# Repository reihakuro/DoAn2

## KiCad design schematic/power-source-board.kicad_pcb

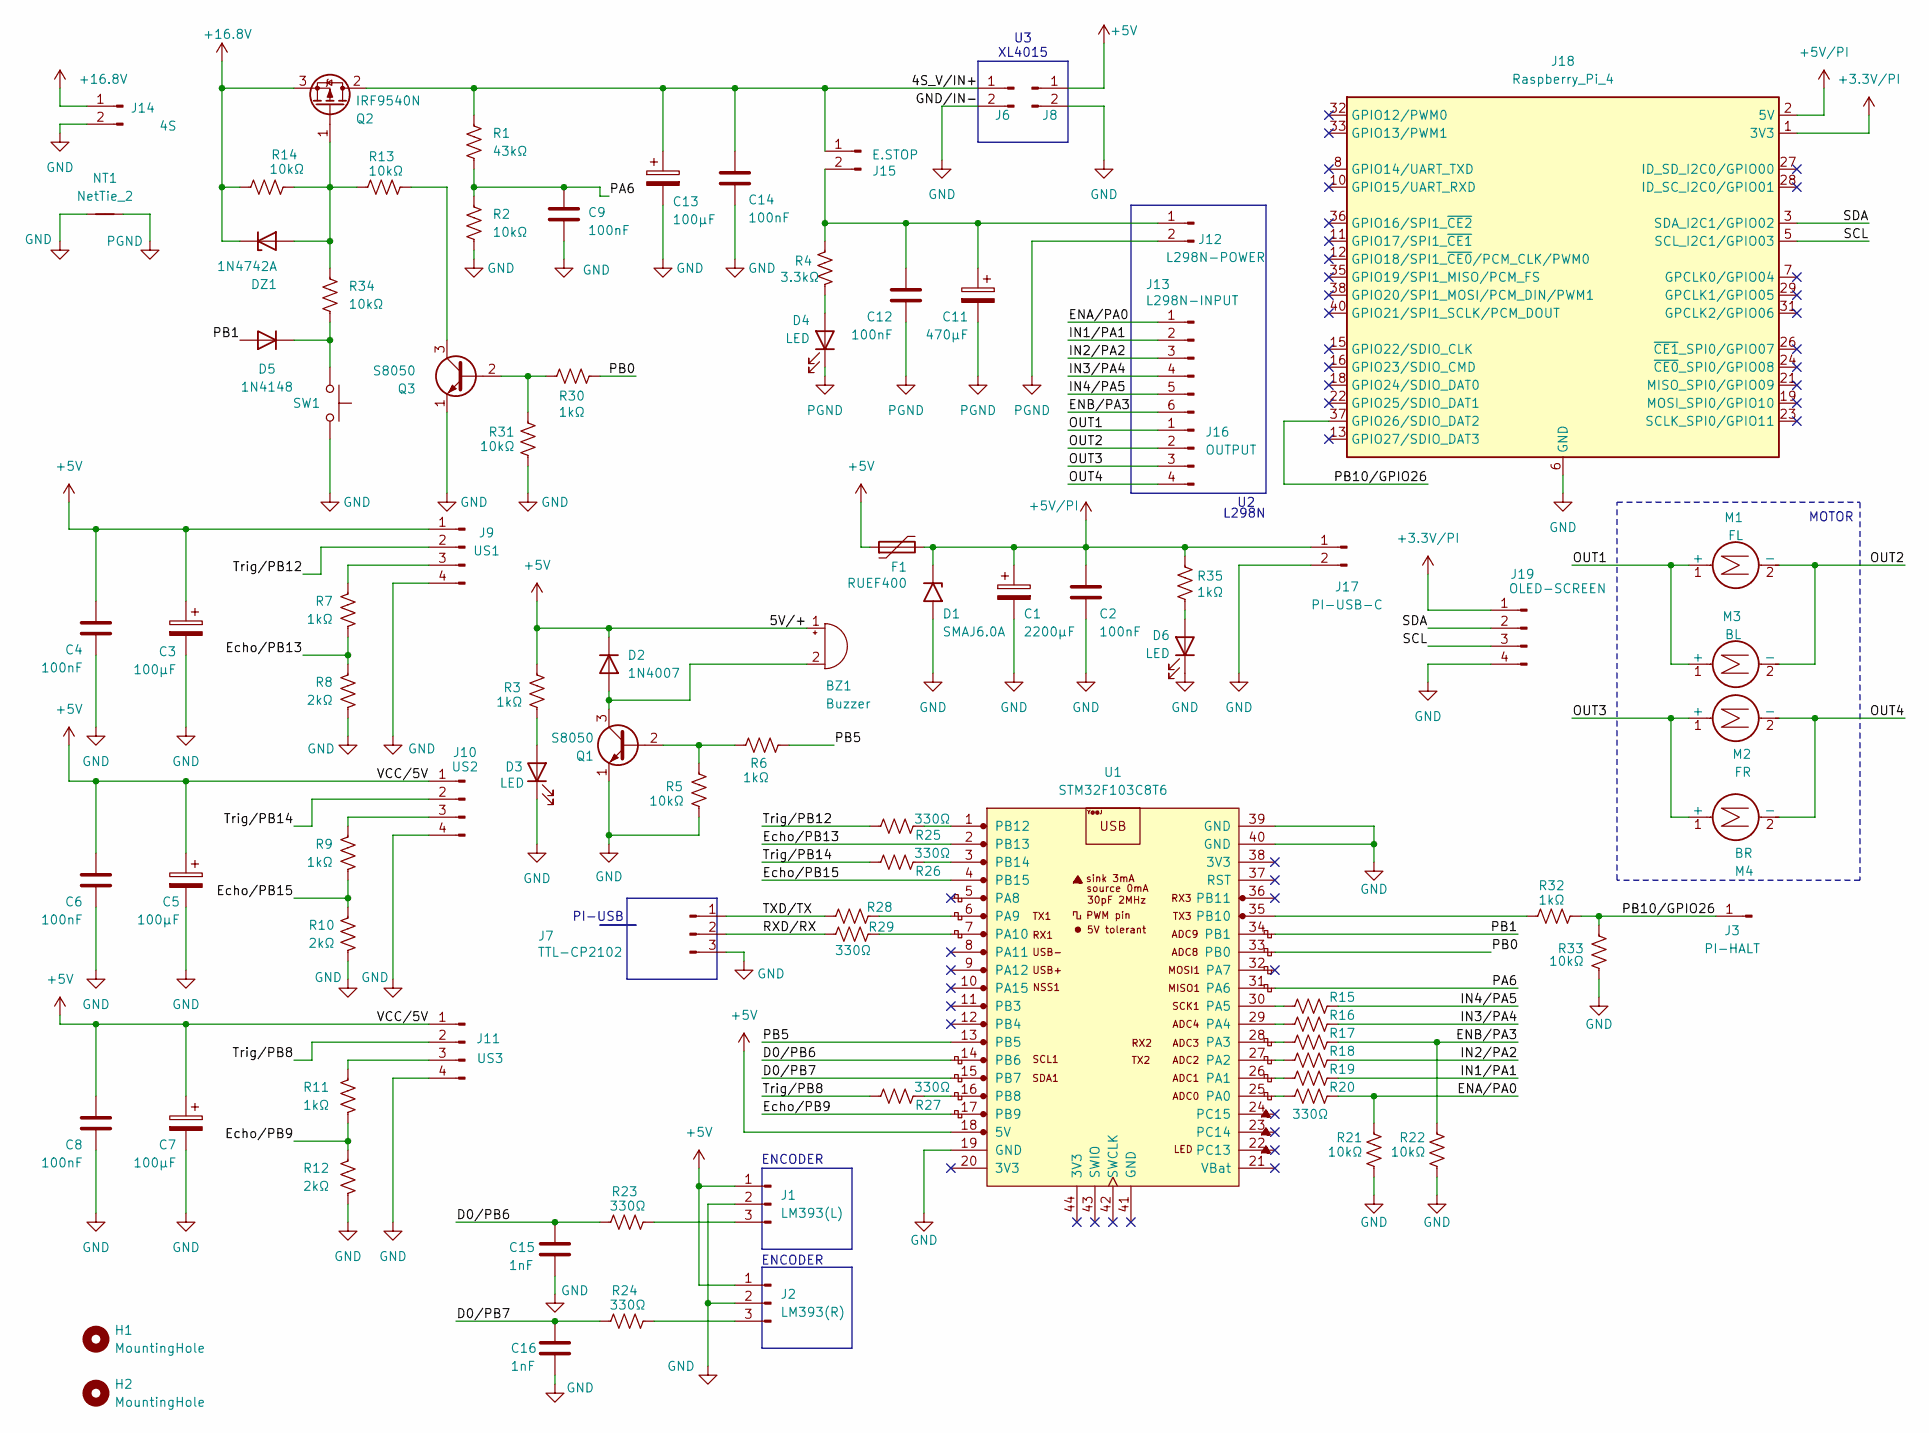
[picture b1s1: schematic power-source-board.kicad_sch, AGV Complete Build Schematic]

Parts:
BZ1: Buzzer; MagneticBuzzer_PUI_AT-0927-TT-6-R
C1: 2200µF; CP_Radial_D10.0mm_P5.00mm
C2, C4, C6, C8, C9, C12, C14: 100nF; C_Disc_D5.0mm_W2.5mm_P2.50mm
C3, C5, C7, C13: 100µF; CP_Radial_D6.3mm_P2.50mm
C11: 470µF; CP_Radial_D8.0mm_P3.50mm
C15, C16: 1nF; C_Disc_D5.0mm_W2.5mm_P2.50mm
D1: SMAJ6.0A; D_SMA
D2: 1N4007; D_DO-41_SOD81_P10.16mm_Horizontal
D3, D4, D6: LED; LED_D3.0mm_Clear
D5: 1N4148; D_DO-41_SOD81_P10.16mm_Horizontal
DZ1: 1N4742A; D_DO-41_SOD81_P10.16mm_Horizontal
F1: RUEF400; Fuse_Bourns_MF-RHT400
H1, H2: MountingHole; MountingHole_3.2mm_M3
J1: LM393(L); PinHeader_1x03_P2.54mm_Vertical
J2: LM393(R); PinHeader_1x03_P2.54mm_Vertical
J3: PI-HALT; PinHeader_1x01_P1.00mm_Horizontal
J6, J8: Conn_01x02_Pin; TerminalBlock_Phoenix_MKDS-1,5-2-5.08_1x02_P5.08mm_Horizont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
J7: TTL-CP2102; PinHeader_1x03_P2.54mm_Vertical
J9: US1; PinHeader_1x04_P2.54mm_Vertical
J10: US2; PinHeader_1x04_P2.54mm_Vertical
J11: US3; PinHeader_1x04_P2.54mm_Vertical
J12: L298N-POWER; TerminalBlock_Phoenix_MKDS-1,5-2-5.08_1x02_P5.08mm_Horizont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
J13: L298N-INPUT; PinHeader_1x06_P2.54mm_Vertical
J14: 4S; TerminalBlock_Phoenix_MKDS-1,5-2-5.08_1x02_P5.08mm_Horizont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
J15: E.STOP; TerminalBlock_Phoenix_MKDS-1,5-2-5.08_1x02_P5.08mm_Horizont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
J16: OUTPUT
J17: PI-USB-C; TerminalBlock_Phoenix_MKDS-1,5-2-5.08_1x02_P5.08mm_Horizont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
J18: Raspberry_Pi_4
J19: OLED-SCREEN
M1: FL
M2: FR
M3: BL
M4: BR
NT1: NetTie_2; NetTie-2_SMD_Pad0.5mm
Q1, Q3: S8050; TO-92_Inline
Q2: IRF9540N; TO-220-3_Vertical
R1: 43kΩ; R_Axial_DIN0207_L6.3mm_D2.5mm_P7.62mm_Horizontal
R2, R5, R13, R14, R21, R22, R31, R33, R34: 10kΩ; R_Axial_DIN0207_L6.3mm_D2.5mm_P7.62mm_Horizontal
R3, R6, R7, R9, R11, R30, R32, R35: 1kΩ; R_Axial_DIN0207_L6.3mm_D2.5mm_P7.62mm_Horizontal
R4: 3.3kΩ; R_Axial_DIN0207_L6.3mm_D2.5mm_P7.62mm_Horizontal
R8, R10, R12: 2kΩ; R_Axial_DIN0207_L6.3mm_D2.5mm_P7.62mm_Horizontal
R15, R16, R17, R18, R19, R20, R23, R24, R25, R26, R27, R28, R29: 330Ω; R_Axial_DIN0207_L6.3mm_D2.5mm_P7.62mm_Horizontal
SW1: A; SW_SPST_Omron_B3F-40xx
U1: STM32F103C8T6; YAAJ_BluePill_2

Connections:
+5V: BZ1.1 (+), C3.1, C4.1, C5.1, C6.1, C7.1, C8.1, D2.1 (K), F1.1, J1.1, J2.1, J8.1, J9.1, J10.1, J11.1, R3.1, U1.18 (5V)
+5V/PI: C1.1, C2.1, D1.1 (A1), F1.2, J17.1, J18.2 (5V), J18.4 (5V), R35.2
+16.8V: DZ1.1 (K), J14.1, Q2.3 (S), R14.1
/4S_V/IN+: C13.1, C14.1, J6.1, J15.1, Q2.2 (D), R1.1
/<NO NET>: J10.2, R26.1
/D0/PB6: C15.1, R23.2, U1.14 (PB6)
/D0/PB7: C16.1, R24.2, U1.15 (PB7)
/ENA/PA0: J13.1, R20.2, R21.2
/ENB/PA3: J13.6, R17.2, R22.2
/Echo/PB9: R11.2, R12.1, U1.17 (PB9)
/Echo/PB13: R7.2, R8.1, U1.2 (PB13)
/Echo/PB15: R9.2, R10.1, U1.4 (PB15)
/IN1/PA1: J13.2, R19.2
/IN2/PA2: J13.3, R18.2
/IN3/PA4: J13.4, R16.2
/IN4/PA5: J13.5, R15.2
/PA6: C9.1, R1.2, R2.1, U1.31 (PA6)
/PB0: R30.1, U1.33 (PB0)
/PB1: D5.2 (A), U1.34 (PB1)
/PB5: R6.1, U1.13 (PB5)
/PB10/GPIO26: J3.1 (Pin_1_1), J18.37 (GPIO26/SDIO_DAT2), R32.2, R33.2
/RXD/RX: J7.2, R29.1
/TXD/TX: J7.1, R28.1
/Trig/PB8: J11.2, R27.1
/Trig/PB12: J9.2, R25.1
GND: C1.2, C2.2, C3.2, C4.2, C5.2, C6.2, C7.2, C8.2, C9.2, C13.2, C14.2, C15.2, C16.2, D1.2 (A2), D3.1 (K), D6.1 (K), J1.2, J2.2, J6.2, J7.3, J8.2, J9.4, J10.4, J11.4, J14.2, J17.2, J18.6 (GND), J18.9 (GND), J18.14 (GND), J18.20 (GND), J18.25 (GND), J18.30 (GND), J18.34 (GND), J18.39 (GND), J19.4, NT1.2, Q1.1 (E), Q3.1 (E), R2.2, R5.2, R8.2, R10.2, R12.2, R21.1, R22.1, R31.2, R33.1, SW1.1, U1.19 (GND), U1.39 (GND), U1.40 (GND)
unnamed: BZ1.2 (-), D2.2 (A), Q1.3 (C)
unnamed: D3.2 (A), R3.2
unnamed: D4.2 (A), R4.1
unnamed: D5.1 (K), R34.2, SW1.2
unnamed: D6.2 (A), R35.1
unnamed: DZ1.2 (A), Q2.1 (G), R13.1, R14.2, R34.1
unnamed: J1.3, R23.1
unnamed: J2.3, R24.1
unnamed: J9.3, R7.1
unnamed: J10.3, R9.1
unnamed: J11.3, R11.1
unnamed: C11.1, C12.1, J12.1, J15.2, R4.2
unnamed: J16.1, M1.1 (+), M3.1 (+)
unnamed: J16.2, M1.2 (-), M3.2 (-)
unnamed: J16.3, M2.1 (+), M4.1 (+)
unnamed: J16.4, M2.2 (-), M4.2 (-)
unnamed: J18.1 (3V3), J18.17 (3V3), J19.1
unnamed: J18.3 (SDA_I2C1/GPIO02), J19.2
unnamed: J18.5 (SCL_I2C1/GPIO03), J19.3
unnamed: Q1.2 (B), R5.1, R6.2
unnamed: Q3.2 (B), R30.2, R31.1
unnamed: Q3.3 (C), R13.2
unnamed: R20.1, U1.25 (PA0)
unnamed: R19.1, U1.26 (PA1)
unnamed: R18.1, U1.27 (PA2)
unnamed: R17.1, U1.28 (PA3)
unnamed: R16.1, U1.29 (PA4)
unnamed: R15.1, U1.30 (PA5)
unnamed: R28.2, U1.6 (PA9)
unnamed: R29.2, U1.7 (PA10)
unnamed: R27.2, U1.16 (PB8)
unnamed: R32.1, U1.35 (PB10)
unnamed: R25.2, U1.1 (PB12)
unnamed: R26.2, U1.3 (PB14)
PGND: C11.2, C12.2, D4.1 (K), J12.2, NT1.1

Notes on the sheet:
ENCODER
MOTOR
PI-USB
L298N
XL4015

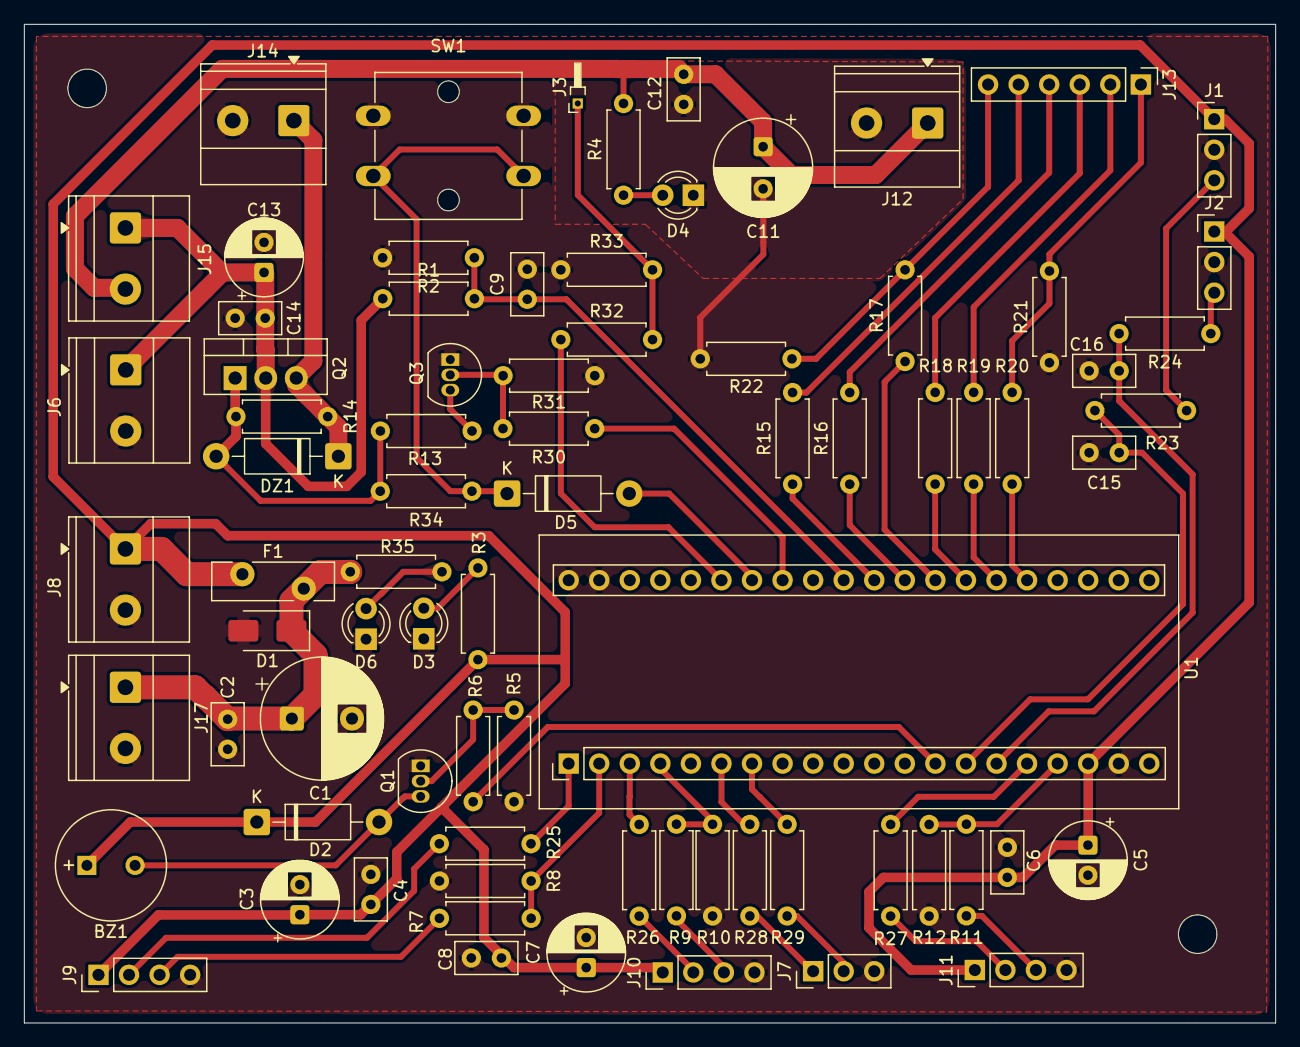
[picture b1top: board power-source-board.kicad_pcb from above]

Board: 2 copper layers, 104.0 x 83.0 mm, 81 parts (0 on the bottom side), 54 nets.

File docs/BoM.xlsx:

DANH SÁCH LINH KIỆN
STT | Tên |  | Thông số | SL | ĐV
1 | U1 | Bo mạch vi điều khiển STM32F103C8T6 | Blue Pill ARM Cortex-M3 72MHz, 64KB Flash, 20KB RAM | 1 | Cái
2 | US1, US2, US3 | Cảm biến khoảng cách siêu âm HC-SR04 | Tần số siêu âm 40kHz, dải đo 2cm - 400cm, góc quét 15 độ | 3 | Cái
3 | J1, J2 (LM393) | Module cảm biến đĩa quang chữ U LM393 | Khe quang điện rộng 5mm, tích hợp IC so sánh LM393 xuất xung D0 | 2 | Cái
4 | Khung xe | Bộ khung xe robot 4 bánh mica 2 tầng | Mica cứng chịu lực 3mm, khung chữ nhật 2 tầng kèm ốc trụ | 1 | Bộ
 |  | Bánh xe cao su địa hình cho động cơ TT | Đường kính 65mm, bản rộng 27mm, vành nhựa lốp cao su bám sàn | 4 | Cái
 |  | Đĩa xung quang học Encoder 20 nan | Đĩa nhựa kỹ thuật màu đen 20 rãnh nan hoa, khớp trục động cơ TT | 4 | Cái
 |  | Động cơ giảm tốc DC TT | Điện áp hoạt động 3V - 9V DC, tỷ số truyền 1:48, trục ra kép | 4 | Cái
5 | U2 | Module Driver điều khiển động cơ L298N | Module cầu H kép L298N, dòng đỉnh 2A/kênh, tích hợp tản nhiệt nhôm | 1 | Cái
6 | BT1, BT2, BT3, BT4, BT5 | Cell pin sạc Li-ion 18650 xả cao | Điện áp 3.7V danh định (đầy 4.2V), 2500mAh, dòng xả liên tục >= 10A | 5 | Viên
7 | BAT_HOLDER_3S | Khay pin 3 cell 18650 (3S) nối tiếp | Khay nhựa chịu lực gắn ngoài, có lò xo nối tiếp sẵn, dây ra Đỏ/Đen | 1 | Cái
8 | BAT_HOLDER_2S | Khay pin 2 cell 18650 (2S) nối tiếp | Khay nhựa chịu lực gắn ngoài, có lò xo nối tiếp sẵn, dây ra Đỏ/Đen | 1 | Cái
9 | CHG1 | Dock sạc đôi pin 18650 rời cắm điện 220V | Đốc sạc 2 khe cắm điện lưới 220V, dòng sạc 1A/khe, tự ngắt khi đầy 4.2V | 1 | Cái
10 | J3, J4 (SWITCH) | Công tắc bập bênh ON/OFF loại nhỏ (KCD11) | Loại 2 chân 250V/3A, kích thước khoét lỗ 15x10mm | 2 | Cái
11 | J5 (E-STOP) | Nút dừng khẩn cấp cơ khí (Latched E-Stop) | Nút nhấn khóa cơ học (nhấn tự khóa, xoay nhả) phi 16mm | 1 | Cái
12 | PLUG_TYPE_C | Đầu giắc đực USB Type-C hàn dây |  | 1 | Cái
13 | U3 (XL4015) | Module Buck DC-DC XL4015 5A | Điện áp vào 8-36V, ra chỉnh cố định 5.15V, dòng đỉnh 5A có tản nhiệt | 1 | Module
14 | F1 | Cầu chì tự phục hồi (Polyfuse PPTC) | Dòng giữ IH=3.0A, dòng ngắt Itrip=5.0A, Vmax >= 16V, chân cắm DIP 5.08mm | 1 | Con
15 | D1 | Diode TVS triệt xung quá áp ngõ ra Pi 4 | SMAJ6.0A (SMD DO-214AC) hoặc 1.5KE6.8A (DIP), VRWM=6.0V, VBR=6.67V | 1 | Con
16 | SC1, SC2, SC3, SC4 | Bộ trụ đồng đỡ bo và ốc tán M3 | Trụ đồng lục giác đực-cái M3x10mm kèm ốc tán và đệm vặn M3 | 4 | Bộ
17 | C2, C4, C6, C8, C9, C10, C12, C14 | Tụ gốm dập xung cao tần (104) | 100nF (0.1uF) / 50V, tụ gốm tròn bước chân 2.54mm | 8 | Con
18 | C15, C16 | Tụ gốm lọc thông thấp RC Encoder (102) | 1nF / 50V, tụ gốm tròn bước chân 2.54mm | 2 | Con
19 | R15, R16, R17, R18, R19, R20, R23, R24, R25, R26, R27, R28, R29 | Điện trở đệm bảo vệ & lọc 330 ohm | 330 ohm +- 5%, công suất 0.25W, chân cắm Axial bước 7.62mm | 13 | Con
20 | R1, R13 | Điện trở chính xác 10k ohm (Nhánh trên ADC) | 10k ohm +- 1%, màng kim loại chính xác cao, 0.25W, bước 7.62mm | 2 | Con
21 | R2, R14 | Điện trở chính xác 3.3k ohm (Nhánh dưới ADC) | 3.3k ohm +- 1%, màng kim loại chính xác cao, 0.25W, bước 7.62mm | 2 | Con
22 | R7, R9, R11 | Điện trở chính xác 1k ohm (Nhánh trên Echo) | 1k ohm +- 1%, màng kim loại, công suất 0.25W, bước 7.62mm | 3 | Con
23 | R8, R10, R12 | Điện trở chính xác 2k ohm (Nhánh dưới Echo) | 2k ohm +- 1%, màng kim loại, công suất 0.25W, bước 7.62mm | 3 | Con
24 | R5, R21, R22 | Điện trở kéo xuống an toàn 10k ohm | 10k ohm +- 5%, công suất 0.25W, bước 7.62mm | 3 | Con
25 | R3, R4, R6 | Điện trở định thiên & hạn dòng 1k ohm | 1k ohm +- 5%, công suất 0.25W, bước 7.62mm | 3 | Con

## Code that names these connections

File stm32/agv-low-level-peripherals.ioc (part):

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Mcu.Name=STM32F103C(8-B)Tx
Mcu.Package=LQFP48
Mcu.UserName=STM32F103C8Tx
PA0-WKUP.Signal=S_TIM2_CH1_ETR
PA1.GPIOParameters=GPIO_Label
PA1.GPIO_Label=MOTOR_IN1
PA1.Signal=GPIO_Output
PA10.Mode=Asynchronous
PA10.Signal=USART1_RX
PA13.Mode=Serial_Wire
PA13.Signal=SYS_JTMS-SWDIO
PA14.Mode=Serial_Wire
PA14.Signal=SYS_JTCK-SWCLK
PA2.GPIOParameters=GPIO_Label
PA2.GPIO_Label=MOTOR_IN2
PA2.Signal=GPIO_Output
PA3.Signal=S_TIM2_CH4
PA4.GPIOParameters=GPIO_Label
PA4.GPIO_Label=MOTOR_IN3
PA4.Signal=GPIO_Output
PA5.GPIOParameters=GPIO_Label
PA5.GPIO_Label=MOTOR_IN4
PA5.Signal=GPIO_Output
PA6.Signal=ADCx_IN6
PA9.Mode=Asynchronous
PA9.Signal=USART1_TX
PB0.GPIOParameters=PinState,GPIO_Label
PB0.GPIO_Label=PWR_HOLD
PB0.PinState=GPIO_PIN_SET
PB0.Signal=GPIO_Output
PB1.GPIOParameters=GPIO_PuPd,GPIO_Label
PB1.GPIO_Label=PWR_BTN
PB1.GPIO_PuPd=GPIO_PULLUP
PB1.Signal=GPIO_Input
PB10.GPIOParameters=GPIO_PuPd,GPIO_Label
PB10.GPIO_Label=PI_HALT
PB10.GPIO_PuPd=GPIO_PULLDOWN
PB10.Signal=GPIO_Input
PB12.GPIOParameters=GPIO_Label
PB12.GPIO_Label=L_TRIG
PB12.Signal=GPIO_Output
PB13.GPIOParameters=GPIO_Label
PB13.GPIO_Label=L_ECHO
PB13.Signal=GPIO_Input
PB14.GPIOParameters=GPIO_Label
PB14.GPIO_Label=M_TRIG
PB14.Signal=GPIO_Output
PB15.GPIOParameters=GPIO_Label
PB15.GPIO_Label=M_ECHO
PB15.Signal=GPIO_Input
PB5.GPIOParameters=GPIO_Label
PB5.GPIO_Label=BZ
PB5.Signal=GPIO_Output
PB6.GPIOParameters=GPIO_PuPd,GPIO_Label
PB6.GPIO_Label=EN_EXT_L
PB6.GPIO_PuPd=GPIO_PULLUP
PB6.Signal=GPXTI6
PB7.GPIOParameters=GPIO_PuPd,GPIO_Label
PB7.GPIO_Label=EN_EXT_R
PB7.GPIO_PuPd=GPIO_PULLUP
PB7.Signal=GPXTI7
PB8.GPIOParameters=GPIO_Label
PB8.GPIO_Label=R_TRIG
PB8.Signal=GPIO_Output
PB9.GPIOParameters=GPIO_Label
PB9.GPIO_Label=R_ECHO
PB9.Signal=GPIO_Input
PD0-OSC_IN.Mode=HSE-External-Oscillator
PD0-OSC_IN.Signal=RCC_OSC_IN
PD1-OSC_OUT.Mode=HSE-External-Oscillator
PD1-OSC_OUT.Signal=RCC_OSC_OUT
RCC.SYSCLKFreq_VALUE=72000000
RCC.SYSCLKSource=RCC_SYSCLKSOURCE_PLLCLK
board=custom
